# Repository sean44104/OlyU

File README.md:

# OlyU

The OlyU is a variant of the Model-U designed for PhoZL and PhobGCCv2.0.3+ to allow for easier shell compatibility and USB data connection. There are 2 variants:

### Type 1 - OlyU-Small

### Type 2 - OlyU-Big

# Overview
Both of these boards feature 8 pads. 6 of these pads connect to the GameCube Controller's standard 6 connections for the main cable. The other 2 pads are for USB Data + and -
The shape and alignment of these pads are designed so that installation is easy and does not require any wire stretching across the board. Both of these boards are compatible with PhobGCC and OEM gamecube controllers, but the USB data pins are specifically designed for the PhobGCC and PhoZL (https://github.com/sean44104/phozl)
If you install one of these onto an oem, or a phob WITHOUT the USB Data, the only thing the OlyU will do is allow you to use USB-C to GCC Cables. If you are on a PhoZL / Phob and you connect the data pins, you can flash your controllers firmware from the USB-C port, use HOJA firmware, and much more!

### Install

# PCB Differences
The OlyU Small version is designed to be installed so that the USB-C port is sandwiched between the main pcb and the OlyU pcb. This way, you can use 2mm pin headers for the installation. It has also been reshaped to perfectly fit with the Removable Gate GCC's shell design (https://github.com/sean44104/Removable-Gate-GCC). Use this version if you are working with custom resin printed shell designs, or if you just want a smaller and more sleak experience!

The OlyU Big version is shaped just like a standard Model-U. Instead of the USB-C port being in between the 2 PCBs, the order goes PCB,PCB,Port. The PCB is designed this way to allow for easy installation into OEM Gamecube Shells with minimal cutting. However, this makes installation slightly more tricky. Use this version if you have parts that were designed around the original Model-U

Both boards have their USB Data pads aligned perfectly with the main PhoZL and PhobGCC PCB

# NOTE
When ordering these boards on JLCPCB, make sure that your SMT Assembly is BOTTOM for OlyU-Small and TOP for OlyU-Big. Every other setting can be left default, and the finish can be whatever you prefer

# License
This project is licenced under the GNU GPL Version 3. [See the included LICENSE file for details](LICENSE).

# Crane's Lab

Model-U is a circuit board for adding USB-C to custom controllers originally created by Crane.
Please support him here:
https://www.paypal.com/donate/?hosted_button_id=NFDEML5FKR8N8

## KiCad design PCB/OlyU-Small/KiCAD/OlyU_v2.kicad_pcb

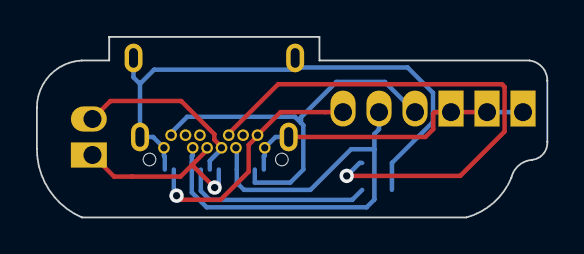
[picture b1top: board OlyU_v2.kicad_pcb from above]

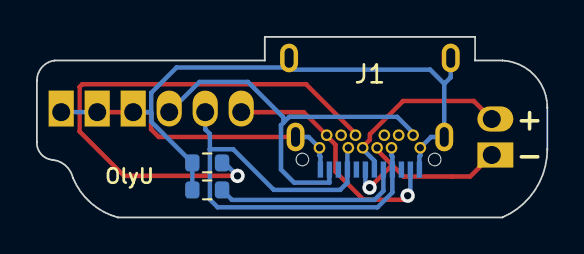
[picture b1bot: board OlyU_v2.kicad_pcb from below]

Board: 2 copper layers, 28.4 x 10.0 mm, 5 parts (3 on the bottom side), 8 nets.

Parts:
J1: USB_C_Receptacle; Shou Han Type-C 24P QCHT
J2: Conn_01x06; PinHeader_1x06_P2.00mm_Vertical
J3: Conn_01x02; PinHeader_1x02_P2.00mm_Vertical
R1, R2: 5.1k; R_0603_1608Metric

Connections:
3V3: J1.A2, J1.B2, J2.1
D3V: J1.A11, J1.B11, J2.3
D+: J1.A6, J1.B6, J3.2
D-: J1.A7, J1.B7, J3.1
GND: J1.A1, J1.A12, J1.B1, J1.B12, J1.S1, J2.4, J2.5, J2.6, R1.1, R2.2
unnamed: J1.A5, R1.2
unnamed: J1.B5, R2.1
VBUS: J1.A4, J1.A9, J1.B4, J1.B9, J2.2

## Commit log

2023-01-14 Initial
2023-01-14 images
2023-01-14 readme
2023-01-14 v1.1 update
    finalizing data placement and silkscreens
2024-06-21 updated the readme
